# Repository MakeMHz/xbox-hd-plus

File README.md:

<h1 align="center">
  <br>
  
  <br>
</h1>
<h4 align="center">The first and only purely digital video output mod for the original Microsoft Xbox.</h4>
<p align="center">

</p>
<p align="center">
  <a href="#about">About</a> •
  <a href="#features">Features</a> •
  <a href="#installation">Installation</a> •
  <a href="#software">Software</a> •
  <a href="#hardware">Hardware</a> •
  <a href="#licensing">Licensing</a>
</p>

## About
The first and only purely digital video output mod for the original Microsoft Xbox. Video is captured directly off of the pixel data bus from the GPU, encoded, and sent directly to your HD TV with no added interpolation or frame-buffering for a crystal clear, no added lag, video output.

But pixel-perfect video isn't all the XboxHD+ offers. Audio is captured from the Xbox's digital SPDIF audio and output over the HDMI connector, and with the correct receiver allow for 5.1 Dolby Digital audio on select games.

XboxHD+ has been in development for over a year and fully tested on every board variation and revision.

## Features
XboxHD+ was designed from the ground up to be the best possible solution for your original Xbox.

  *  Pixel perfect digital video. Supports all official Xbox video resolutions. (480i, 480p, 576i, 720P, and 1080i)
  *  Crystal clear digital audio with surround-sound and Dolby Digital pass-through.
  *  Upgradable firmware via our Xbox application for additional future features, bug fixes, etc!
  *  HDMI CEC support.
  *  Completely reversible! 100% no-cut mod.
  *  Optional force 480P. (Force 480i games to run in 480p)
  *  Optional auto anamorphic widescreen for widescreen 480P content. By default, 16:9 480P content will be stretched to fullscreen as the game intended. Avoid the hassle of having to adjust your TV's zoom/aspect ratio when switch between widescreen and none-widescreen 480P games.

## Installation
**Stellar XboxHD+**

[Upgrading to Stellar XboxHD+](https://support.makemhz.com/xbox-hdmi/upgrade/stellar)

[Installation Manual (Stellar XboxHD+ v2 1.0 - 1.5)](https://support.makemhz.com/xbox-hdmi/installation/stellar-xboxhd-1-0)

[Installation Manual (Stellar XboxHD+ v2 1.6)](https://support.makemhz.com/xbox-hdmi/installation/stellar-xboxhd-1-6)

**XboxHD+**

[Installation Manual (XboxHD+ 1.0 - 1.5)](https://support.makemhz.com/xbox-hdmi/installation/xboxhd-1-0)

[Installation Manual (XboxHD+ 1.6)](https://support.makemhz.com/xbox-hdmi/installation/xboxhd-1-6)

**XboxHDMI**

[Installation Manual (XboxHDMI 1.0 - 1.5)](https://support.makemhz.com/xbox-hdmi/installation/xboxhdmi-1-0)

[Installation Manual (XboxHDMI 1.6)](https://support.makemhz.com/xbox-hdmi/installation/xboxhdmi-1-6)

## Software
Configuration and firmware updates are preformed using the XboxHD+ homebrew app. For Stellar XboxHD+ everything is handled via StellarOS.

See [MakeMHz/xbox-hd-plus-app](https://github.com/MakeMHz/xbox-hd-plus-app) (For XboxHD+ installs)

See [MakeMHz/xbox-hdmi-app](https://github.com/MakeMHz/xbox-hdmi-app) (For XboxHDMI installs)

## Hardware
### QSB Fix (1.0/1.1)
[KiCad Project](board/1_0_fix)

### 3D Printed Parts
The XboxHD+ kit includes two 3D printed parts. Parts are designed in Fusion360 and can be downloaded in multiple formats from the links below.

[HDMI Panel](https://raw.githubusercontent.com/MakeMHz/xbox-hd-plus/master/stl/Case%20Filler.stl)

[Board Spacer](https://raw.githubusercontent.com/MakeMHz/xbox-hd-plus/master/stl/Board%20Spacer.stl)

## Licensing
Parts of XboxHD+ are free and open source with plans to release everything else in the near future. Please respect the licenses available in their respective folders.

Hardware is shared under the CERN OHL version 1.2.
 
XboxHD+ configuration app was made with NXDK and is shared under GPLv2.

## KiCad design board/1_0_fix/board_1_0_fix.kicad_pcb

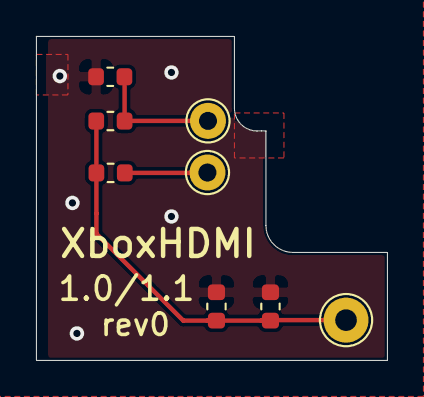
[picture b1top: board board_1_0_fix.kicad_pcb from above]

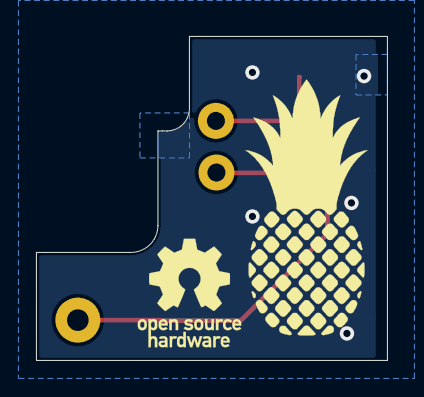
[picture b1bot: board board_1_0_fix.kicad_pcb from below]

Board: 2 copper layers, 19.5 x 18.0 mm, 10 parts (2 on the bottom side), 4 nets.

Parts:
C1, C2: C; C_0603_1608Metric
LOGO1: Logo_Open_Hardware_Small; OSHW-Logo_5.7x6mm_SilkScreen
LOGO2: C; logo
R4B7: 100; R_0603_1608Metric
R4M7, R4N14: 200; R_0603_1608Metric
TP1: TestPoint; TestPoint_THTPad_D2.5mm_Drill1.2mm
TP2, TP3: TestPoint; TestPoint_THTPad_D2.0mm_Drill1.0mm

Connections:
CLKI: R4M7.2, R4N14.1, TP3.1
FIELD: R4B7.2, TP2.1
GND: C1.2, C2.2, R4N14.2
VIDEO_1v5: C1.1, C2.1, R4B7.1, R4M7.1, TP1.1

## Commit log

2020-11-23 Add Youtube watch image
2020-11-23 Add schematic for Xbox 1.1 GPU encoder section
2020-11-23 Add schematic for Xbox 1.6 GPU encoder section
2020-11-23 Add installation manual
2020-11-23 Fix typo in installation manual
2020-11-23 Change wording for installation manual
    Rewrote the part about 'ample flex'
2020-11-23 Create LICENSE
2020-12-02 Fix jumper wires in Installation Manual
2020-12-06 Import of M0RPH10U5 markdown rewrite
2020-12-06 Rename markdown file
2020-12-06 Fix broken image for Youtube video
    Replaced image with a high resolution one
2020-12-06 Change PDF guide to `This guide has moved`
2020-12-07 Rewrite PDF guide as markdown (#4)
    * Import of M0RPH10U5 markdown rewrite
    * Rename markdown file
    * Fix broken image for Youtube video
    Replaced image with a high resolution one
    * Change PDF guide to `This guide has moved`
2020-12-07 Add m8plus IPS patch
2020-12-07 Mockup README.md for kernel patches
2020-12-07 Add patch guide images
2020-12-07 Add warning to kernel patch
2020-12-07 Feature patches (#5)
    * Mockup README.md for kernel patches
    * Add patch guide images
    * Create Kernel Patch - m8plus.md
    * Add warning to kernel patch
2020-12-07 Fix images in Kernel Patch - m8plus
2020-12-07 Add links to guide in patches README.md
2020-12-07 Update patch install link
2020-12-07 Update Kernel Patch - m8plus.md
    Fixed some small typos
2020-12-07 Update Kernel Patch - m8plus.md (#6)
    Fixed some small typos
2020-12-22 Initial design
    Design rev 0 for the Xbox 1.0-1.1 fix
2020-12-30 Mockup Support.md
2021-01-04 Update Kernel Patch - m8plus.md
    Added 'Files of type' step.
2021-01-04 Update Kernel Patch - m8plus.md (#10)
    Added 'Files of type' step.
2021-01-06 Fix board layout for production
    Small adjustments to layout for the production run of rev0
2021-01-10 Add verified m8plus BIOS variants to patch list
    Added verified m8plus BIOS variants from the LBA48 patched set.
2021-01-10 Fix timing edge-cases in kernel patch
2021-01-10 Bump kernel patch version to 1.2.2
2021-02-07 Add installation manual for 1.6
2021-02-07 Remove PDF guide
2021-02-07 Rename installation manual files
2021-02-07 Add QSB installation manual
2021-02-07 Fix typo
    :P
2021-02-08 Board 1 0 fix (#12)
    * Initial design
    Design rev 0 for the Xbox 1.0-1.1 fix
    * Fix board layout for production
    Small adjustments to layout for the production run of rev0
2021-02-08 Add links to 3D printable parts
2021-02-15 Add color symbols to the QSB connection table
2021-02-15 Add PCB layout image to the QSB manual
2021-02-17 Correct QSB graphic for CLKI pin
2021-02-20 Add 'pre-shaping' note to installation manual
2021-02-20 Add 'HDTV AV/component cable' requirement to installation manual
2021-03-02 Added essential links and FAQs to the readme.
2021-03-02 Update the link text for the 1.6 installation manual.
2021-03-02 Rewrite README.md
2021-03-02 Add 1.3.1 patch for m8plus
2021-03-02 Add patch note regarding 1.6 game compatibility
2021-03-02 Remove HDTV cable requirement for testing BIOS patch in manual
2021-03-02 Add BIOS patch notes to 1.6 manual
2021-03-02 Cleanup manuals
    Small formatting changes
2021-03-09 Add Hexen 2018 m8plus hash to patch list
2021-03-15 Update Installation Manual (Xbox Revision 1.6).md
    Fix two (minor) typos.
2021-03-27 Fix kernel patch not sending correct encoder id
2021-03-31 Remove references to 1.8v wire in the 1.6 installation manual
2021-03-31 Remove reference to 1.8v wire in the 1.6 installation manual
2021-04-09 Update logo
2021-04-09 Change naming to XboxHD+
2021-04-09 Add Identifying Xbox Revision guide
2021-04-18 Fix GND point in QSB image
2021-04-20 Update m8plus BIOS patch to 1.4.3
    Adds preliminary support for upscaling.
2021-04-20 Add iND BIOS patch
2021-06-24 Update Installation Manual (Xbox Revision 1.6).md (#15)
    Fix two (minor) typos.
2021-07-13 Fix "connect" typo
2021-07-13 Add additional warning section to "Preparation"
2021-07-13 Fix "preparation" typo
2021-07-13 Add additional flex positioning warning
2021-08-01 Add kpatch and documentation to the patches README.md
2021-08-01 Add HD+ Software installation guide
2021-08-01 Additional warnings & typos (#21)
    * Add additional warning section to "Preparation"
    * Add additional flex positioning warning
    * Fix "preparation" typo
    * Fix "connect" typo
2021-08-01 Add updated images for guide
2021-08-01 Fix text for software installation
2021-08-02 More grammar fixes
2021-08-02 Rename XboxHDMI guides
2021-08-02 Add XboxHD+ installation guide
2021-08-02 Fix formatting of installation guide
2021-08-02 Add XboxHDMI software installation guide
2021-08-02 Fix typo in XboxHD+ software installation guide
2021-08-02 Rewrite XboxHDMI guides
2021-08-02 Fix link in XboxHD+ 1.6 guide
2021-08-02 Fix grammar mistakes
2021-08-02 Fix guide links
2021-08-02 Fix links to configuration app
2021-08-02 Fix link to kpatch IPS for m8plus
2021-08-03 Add HDD unlock instructions
2021-08-10 Add kpatch v1.0.1 patch
2021-08-10 Remove HDD 'unlock' step
2021-08-10 Add 'Do not skip' warning to step 1 of installation guide
2021-08-10 Add firmware warning
2021-08-10 Fix typos
2021-08-12 Add kpatch v1.0.2 patch
    Fixed issue of 'Error 13' from coldboot if harddrive is locked.
2021-09-07 Add XboxHD+/QSB installation guide
2021-09-07 Emphasize that the HD+ QSB is required for all revisions
2021-09-07 Change installation photo for the HD+ guides to one of the HD+ board
2021-09-07 FIx typos/grammar
2021-09-07 Remove leftover text
2021-09-07 Add link to HD+ 1.0 - 1.5 guide to main README
2021-09-08 Correct QSB troubleshooting test points
2021-10-09 Add programming kit request link to 1.6 installation guide
2022-02-09 Add STL files for 3D printed parts
    Fusion360 removed the export links on project pages, so we'll have to host them here instead.
2022-03-28 Add experimental settings documentation
2022-06-04 Remove reference to 1v8 wire
2022-06-11 Mockup upgrade manual
2022-06-11 Fix image alignment
2022-06-11 Add image to show the links for the BIOS patching guides
2022-06-11 More typos
2022-06-11 Cleanup
2022-06-11 Typos
2022-06-11 Add firmware upgrade instructions
2022-06-11 Fix typos/grammar mistakes
2022-06-11 Add BIOS patch for v2 firmware
2022-06-11 Fix typo
2022-06-11 Revert "Add BIOS patch for v2 firmware"
    This reverts commit 13aca2ba06bc7bf2bbfb11cc49571214fa5f6b91.
2022-06-11 Remove modified file from PR
2022-06-11 Add XboxHDMI upgrade guide (#38)
    * Mockup upgrade manual
    * Fix image alignment
    * Add image to show the links for the BIOS patching guides
    * Fix typos/grammar mistakes
    * Typos
    * Add firmware upgrade instructions
2022-06-12 Fix typos in XboxHDMI upgrade guide
2022-06-19 Update flex reference images
2023-03-30 Add Stellar XboxHD+ installation guides
2023-03-30 Add Upgrading to Stellar XboxHD+ guide
2023-03-31 Add note about SDA/SCL wires for Stellar upgrade
2023-10-12 Move documentation to support.makemhz.com
2023-10-12 Fix missing image in README.md
2024-01-14 Fix patch guide links
